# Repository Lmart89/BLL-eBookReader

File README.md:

# 📘 Bll Pilot

**Bll Pilot** es un proyecto de hardware libre y software de código abierto cuyo propósito es crear un lector de eBooks bíblicos de bajo consumo, enfocado en la simplicidad, portabilidad y larga duración de batería, diseñado especialmente para funcionar en zonas de baja conectividad o para uso personal/devocional.

> ✝️ *“Bll” representa muchas cosas: por un lado, “Biblia de Lectura Libre”, como un enfoque hacia el acceso abierto a la Palabra. Pero también son las iniciales de tres personas que inspiran profundamente este proyecto: Brillyd (esposa), Lemuel (hijo) y Luis (autor). "Pilot" señala que esta es la primera etapa o base para versiones futuras.*

---

## 🚀 Estado del proyecto

✨ **Actualización clave:** Al adoptar el módulo Core 3506B, el proyecto gana notables ventajas:

- 🧠 Procesador Quad-Core para mejor rendimiento multitarea
- 🎨 GPU integrada que mejora la fluidez gráfica incluso en pantallas E-Ink
- 🚀 Duplicación de RAM: de 256MB (anteriormente) a 512MB DDR3L
- 🔌 Mayor cantidad de pines IO (120), facilitando expansión sin conflictos

Estas mejoras colocan al *Bll Pilot* en una posición robusta para futuras funcionalidades sin sacrificar simplicidad ni eficiencia.

🔧 En desarrollo activo – Actualmente se encuentra en fase de diseño de hardware y primeros prototipos físicos.

La primera versión se centrará en:
- Lectura offline de textos bíblicos
- Bajo consumo y pantalla de tinta electrónica
- Interfaz minimalista para navegación fluida

---

## 🔩 Características técnicas

### 🧠 Módulo principal

- **Módulo base:** `Luckfox Core 3506B`
- **Chip:** Rockchip RK3506B
- **Procesador:** 3× Cortex-A7 + 1× Cortex-M0
- **RAM:** 512 MB DDR3L externa
- **Almacenamiento:** eMMC 8 GB por defecto
- **Almacenamiento soportado:** SPI Flash / eMMC / SDMMC
- **RM_IO:** 32 pines Rockchip Matrix IO
- **GPU:** Aceleración 2D/3D integrada
- **Conectividad:** USB host, soporte para Wi-Fi vía dongle USB (o versión Lyra W con Wi-Fi onboard)
- **Dimensiones:** 32 mm × 32 mm
- **Conectores:** 120 pines tipo *stamp hole*

### 🖥️ Pantalla
- Tipo: Pantalla E-Ink ED060XD4 (6 pulgadas, reciclada de Kindle)
- Interfaz: SPI
- Controlador: Requiere PMIC externo (como TPS65185)

### 🔌 Conectividad
- Táctil capacitivo (opcional, vía I2C)
- MicroSD (opcional)
- USB tipo C para carga y datos

### 🔋 Energía
- Batería de polímero de litio (con circuito de protección y carga)
- Circuito de bajo consumo en standby

---

## 📱 Software

El sistema estará basado en:
- 🐧 **Linux embebido** con Buildroot
- 🧱 Interfaz ligera (basada en LVGL o framebuffer directo)
- 📖 Motor de renderizado de textos optimizado para pantallas E-Ink
- 🕮 Indexación de la Biblia en diferentes versiones
- ⛺ Posibilidad de agregar documentos EPUB, TXT o formatos ligeros

---

## 🔓 Licencia

### 🔧 Hardware
Este proyecto está licenciado bajo la **CERN Open Hardware License v2 – Strongly Reciprocal (CERN OHL v2-S)**.

> Esto significa que cualquier derivado del hardware deberá mantenerse igualmente abierto y compartido con la comunidad.

### 💾 Software
El software se publica bajo la **GNU General Public License v3.0 (GPLv3)**.

> Esta licencia protege las libertades de uso, estudio, modificación y distribución del código, asegurando que permanezca siempre libre para todos los usuarios.

---

## 🧭 Visión futura

**Bll Pilot** nace como una plataforma que va más allá de ser un lector de eBooks:

- 📖 Herramienta de estudio bíblico portátil
- ⛺ Recurso para comunidades en zonas rurales o de difícil acceso
- 🛠️ Plataforma educativa para makers que deseen aprender sobre hardware embebido
- 📚 Dispositivo de lectura privada o devocional

Más adelante podrían desarrollarse versiones ampliadas, con audio, conectividad Wi-Fi permanente, y sincronización de notas o planes de lectura.

---

## 🙏 Créditos y agradecimientos

Proyecto impulsado por Luis E. Martínez S., con pasión por la electrónica, la Biblia, y el aprendizaje autodidacta.

Inspirado en la necesidad de crear herramientas útiles, abiertas y accesibles para todos.

> *Soli Deo Gloria.*

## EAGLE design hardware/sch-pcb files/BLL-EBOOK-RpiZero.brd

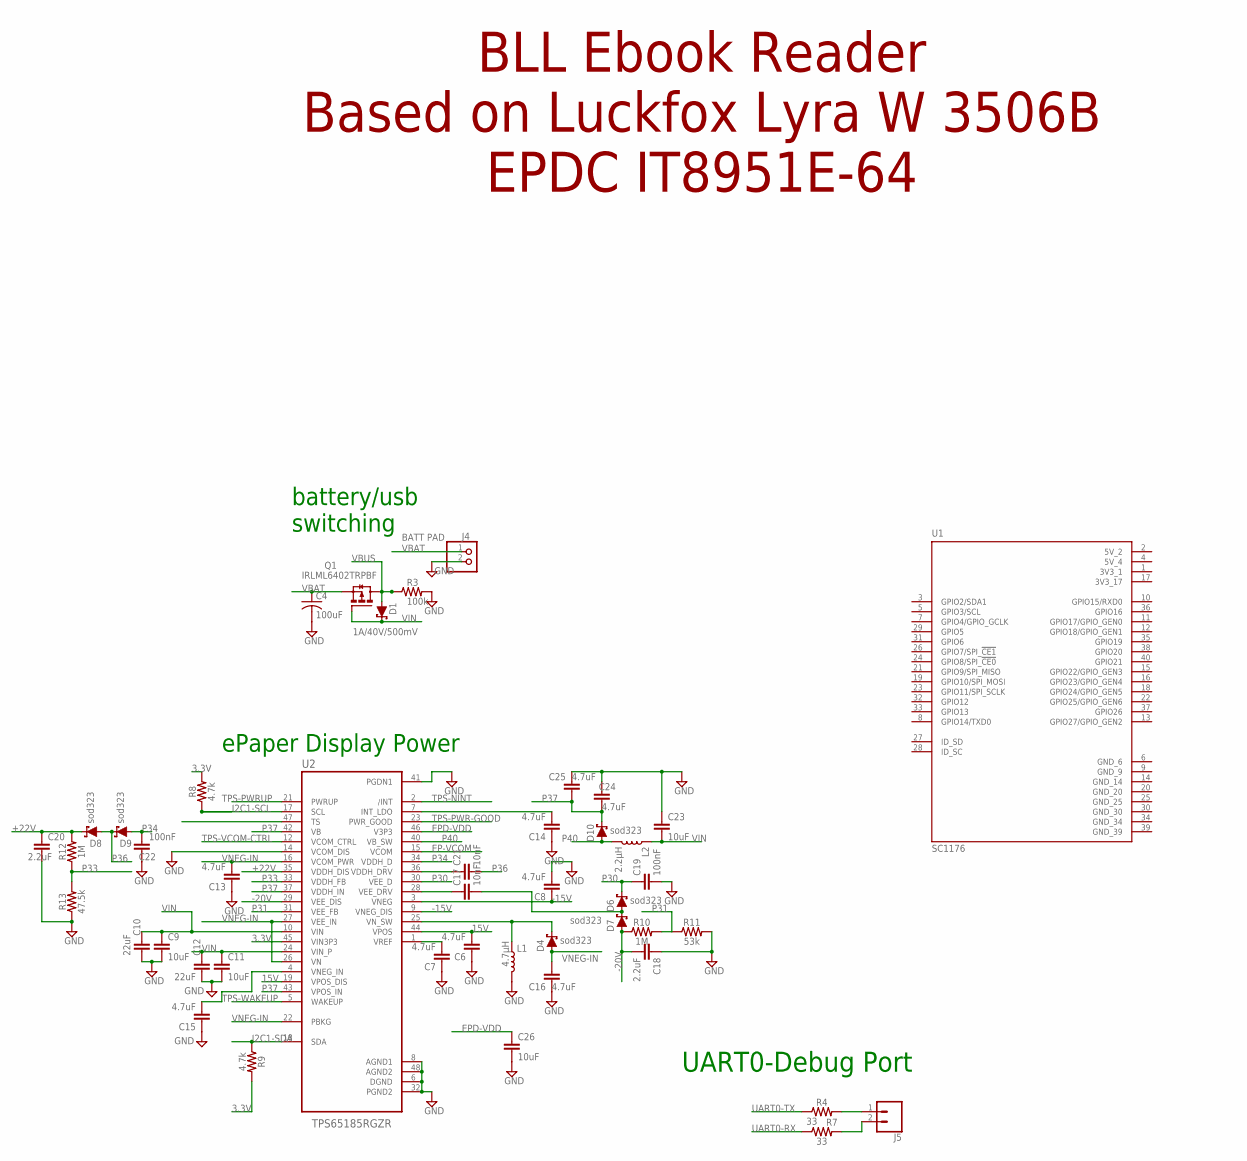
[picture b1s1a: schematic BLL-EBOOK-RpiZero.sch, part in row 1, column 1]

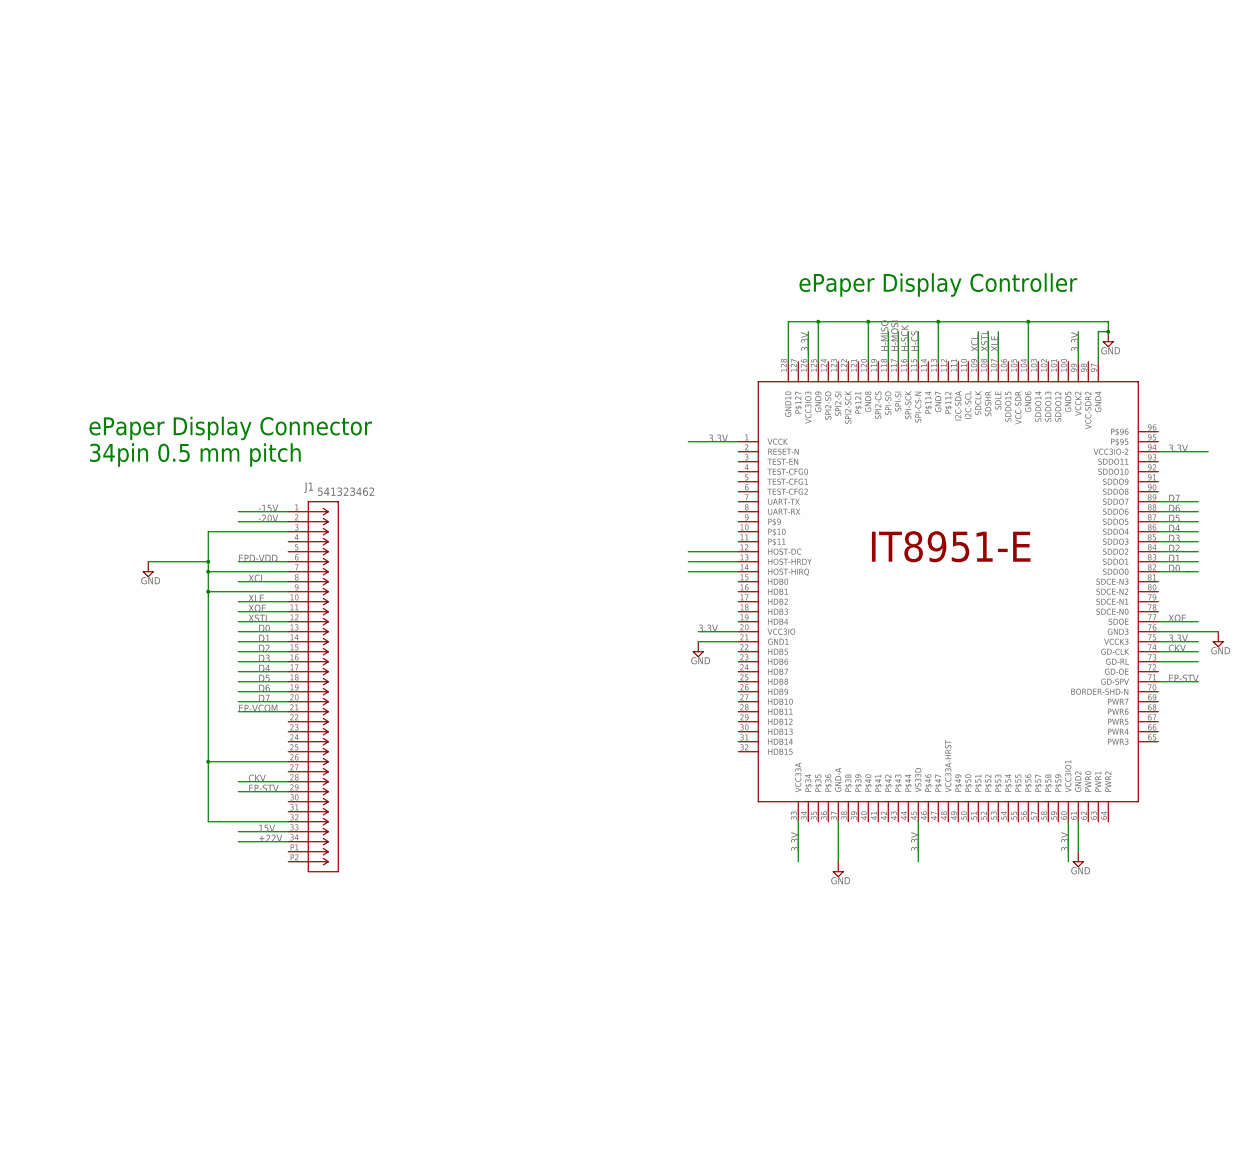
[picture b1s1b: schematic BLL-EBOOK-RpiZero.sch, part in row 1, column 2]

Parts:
C4: 100uF; C0603
C6, C7, C8, C13, C14, C15, C16, C24, C25: 4.7uF; 0603
C9, C11, C23, C26: 10uF; 0805
C10, C12: 22uF; 0805
C17, C21: 10nF; 0603
C18, C20: 2.2uF; 1206
C19, C22: 100nF; 0603
D1: 1A/40V/500mV; SMA-DIODE
D4, D6, D7, D8, D9, D10: sod323; SOD-323
J1: 541323462; CON_541323462_MOL
J4: BATT PAD; 1X02/90
J5: CONN_02LOCK; 1X02_LOCK
L1: 4.7μH; 1008(2520)
L2: 2.2μH; 0806
Q1: IRLML6402TRPBF; SOT23
R3: 100k; R0603
R4, R7: 33; 0603
R8, R9: 4.7k; 0603
R10, R12: 1M; 0603
R11: 53k; 0805
R13: 47.5k; 0805
U1: SC1176; MODULE_SC1176
U2: TPS65185RGZR; QFN50P700X700X100-49N
U$1: IT8951; LQFP128_STM

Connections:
3.3V: R8.2, R9.2, U2.45 (VIN3P3), U$1.1 (VCCK), U$1.20 (VCC3IO), U$1.33 (VCC33A), U$1.45 (VS33D), U$1.60 (VCC3IO1), U$1.75 (VCCK3), U$1.94 (VCC3IO-2), U$1.99 (VCCK2), U$1.126 (VCC3IO3)
3V3_1: U1.1 (3V3_1)
3V3_17: U1.17 (3V3_17)
5V_2: U1.2 (5V_2)
5V_4: U1.4 (5V_4)
15V: C6.2, J1.33, U2.19 (VPOS_DIS), U2.44 (VPOS)
+22V: C20.1, D8.C, J1.34, R12.2, U2.35 (VDDH_DIS)
-15V: C8.1, J1.1, U2.3 (VNEG), U2.9 (VNEG_DIS)
-20V: C18.2, D7.A, J1.2, R10.1, U2.29 (VEE_DIS)
CKV: J1.28, U$1.74 (GD-CLK)
D0: J1.13, U$1.82 (SDDO0)
D1: J1.14, U$1.83 (SDDO1)
D2: J1.15, U$1.84 (SDDO2)
D3: J1.16, U$1.85 (SDDO3)
D4: J1.17, U$1.86 (SDDO4)
D5: J1.18, U$1.87 (SDDO5)
D6: J1.19, U$1.88 (SDDO6)
D7: J1.20, U$1.89 (SDDO7)
EP-STV: J1.29, U$1.71 (GD-SPV)
EP-VCOM: J1.21, U2.15 (VCOM)
EPD-VDD: C26.1, J1.6, U2.46 (V3P3)
GND: C4.2, C6.1, C7.1, C8.2, C9.2, C10.2, C11.2, C12.2, C13.1, C14.1, C15.1, C16.1, C18.1, C19.2, C20.2, C22.1, C23.1, C24.2, C25.2, C26.2, J1.3, J1.7, J1.9, J1.26, J1.32, J4.2, L1.2, R3.2, R11.2, R13.1, U2.6 (DGND), U2.8 (AGND1), U2.14 (VCOM_DIS), U2.32 (PGND2), U2.41 (PGDN1), U2.48 (AGND2), U$1.21 (GND1), U$1.37 (GND-A), U$1.61 (GND2), U$1.76 (GND3), U$1.97 (GND4), U$1.104 (GND6), U$1.113 (GND7), U$1.120 (GND8), U$1.125 (GND9), U$1.128 (GND10)
GND_6: U1.6 (GND_6)
GND_9: U1.9 (GND_9)
GND_14: U1.14 (GND_14)
GND_20: U1.20 (GND_20)
GND_25: U1.25 (GND_25)
GND_30: U1.30 (GND_30)
GND_34: U1.34 (GND_34)
GND_39: U1.39 (GND_39)
H-CS: U$1.115 (SPI-CS-N)
H-MISO: U$1.118 (SPI-SO)
H-MOSI: U$1.117 (SPI-SI)
H-SCK: U$1.116 (SPI-SCK)
I2C1-SCL: R8.1, U2.17 (SCL)
I2C1-SDA: R9.1, U2.18 (SDA)
unnamed: J5.1, R4.2
unnamed: J5.2, R7.2
unnamed: C7.2, U2.1 (VREF)
unnamed: C15.2, U2.4 (VNEG_IN)
unnamed: C14.2, U2.7 (INT_LDO)
unnamed: D4.C, L1.1, U2.25 (VN_SW)
unnamed: C17.1, U2.28 (VEE_DRV)
unnamed: C17.2, D6.A, D7.C
unnamed: C21.1, U2.36 (VDDH_DRV)
P30: C19.1, D6.C, U2.30 (VEE_D)
P31: R10.2, R11.1, U2.31 (VEE_FB)
P33: R12.1, R13.2, U2.33 (VDDH_FB)
P34: C22.2, D9.A, U2.34 (VDDH_D)
P36: C21.2, D8.A, D9.C
P37: C24.1, C25.1, D10.C, U2.37 (VDDH_IN), U2.42 (VB), U2.43 (VPOS_IN)
P40: D10.A, L2.2, U2.40 (VB_SW)
TPS-NINT: U2.2 (/INT)
TPS-PWR-GOOD: U2.23 (PWR_GOOD)
TPS-PWRUP: U2.21 (PWRUP)
TPS-VCOM-CTRL: U2.12 (VCOM_CTRL)
TPS-WAKEUP: U2.5 (WAKEUP)
UART0-RX: R7.1
UART0-TX: R4.1
VBAT: C4.1, J4.1, Q1.2 (S)
VBUS: D1.A, Q1.3 (D), R3.1
VIN: C9.1, C10.1, C11.1, C12.1, C23.2, D1.C, L2.1, Q1.1 (G), U2.10 (VIN), U2.24 (VIN_P)
VNEG-IN: C13.2, C16.2, D4.A, U2.16 (VCOM_PWR), U2.22 (PBKG), U2.26 (VN), U2.27 (VEE_IN)
XCL: J1.8, U$1.109 (SDCLK)
XLE: J1.10, U$1.107 (SDLE)
XOE: J1.11, U$1.77 (SDOE)
XSTL: J1.12, U$1.108 (SDSHR)

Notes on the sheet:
battery/usb switching
ePaper Display Power
ePaper Display Connector 34pin 0.5 mm pitch
BLL Ebook Reader Based on Luckfox Lyra W 3506B EPDC IT8951E-64
ePaper Display Controller
UART0-Debug Port

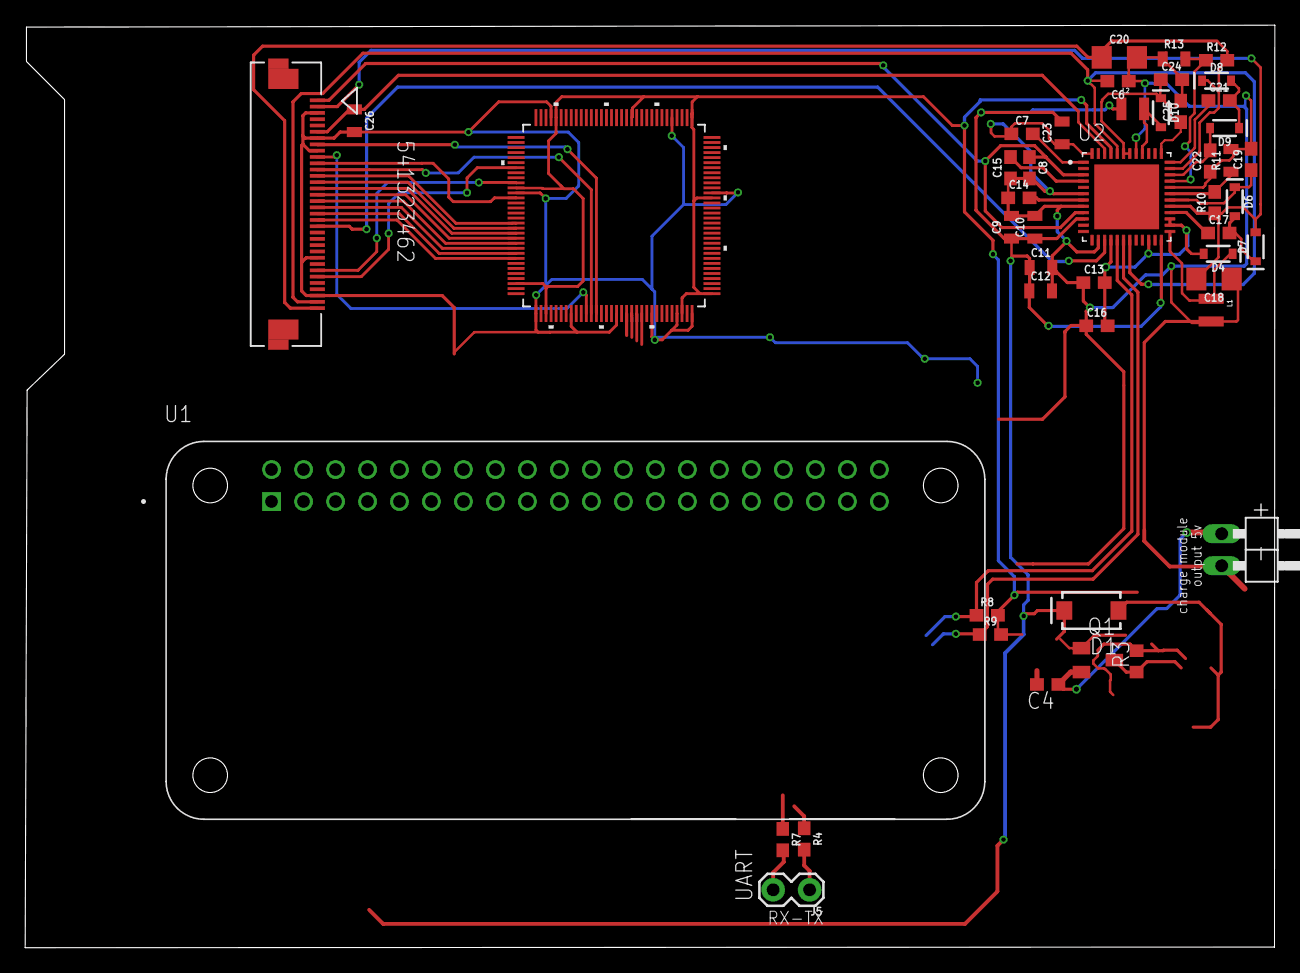
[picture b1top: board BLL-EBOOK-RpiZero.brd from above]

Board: 2 copper layers, 99.2 x 73.2 mm, 47 parts (0 on the bottom side), 44 nets.

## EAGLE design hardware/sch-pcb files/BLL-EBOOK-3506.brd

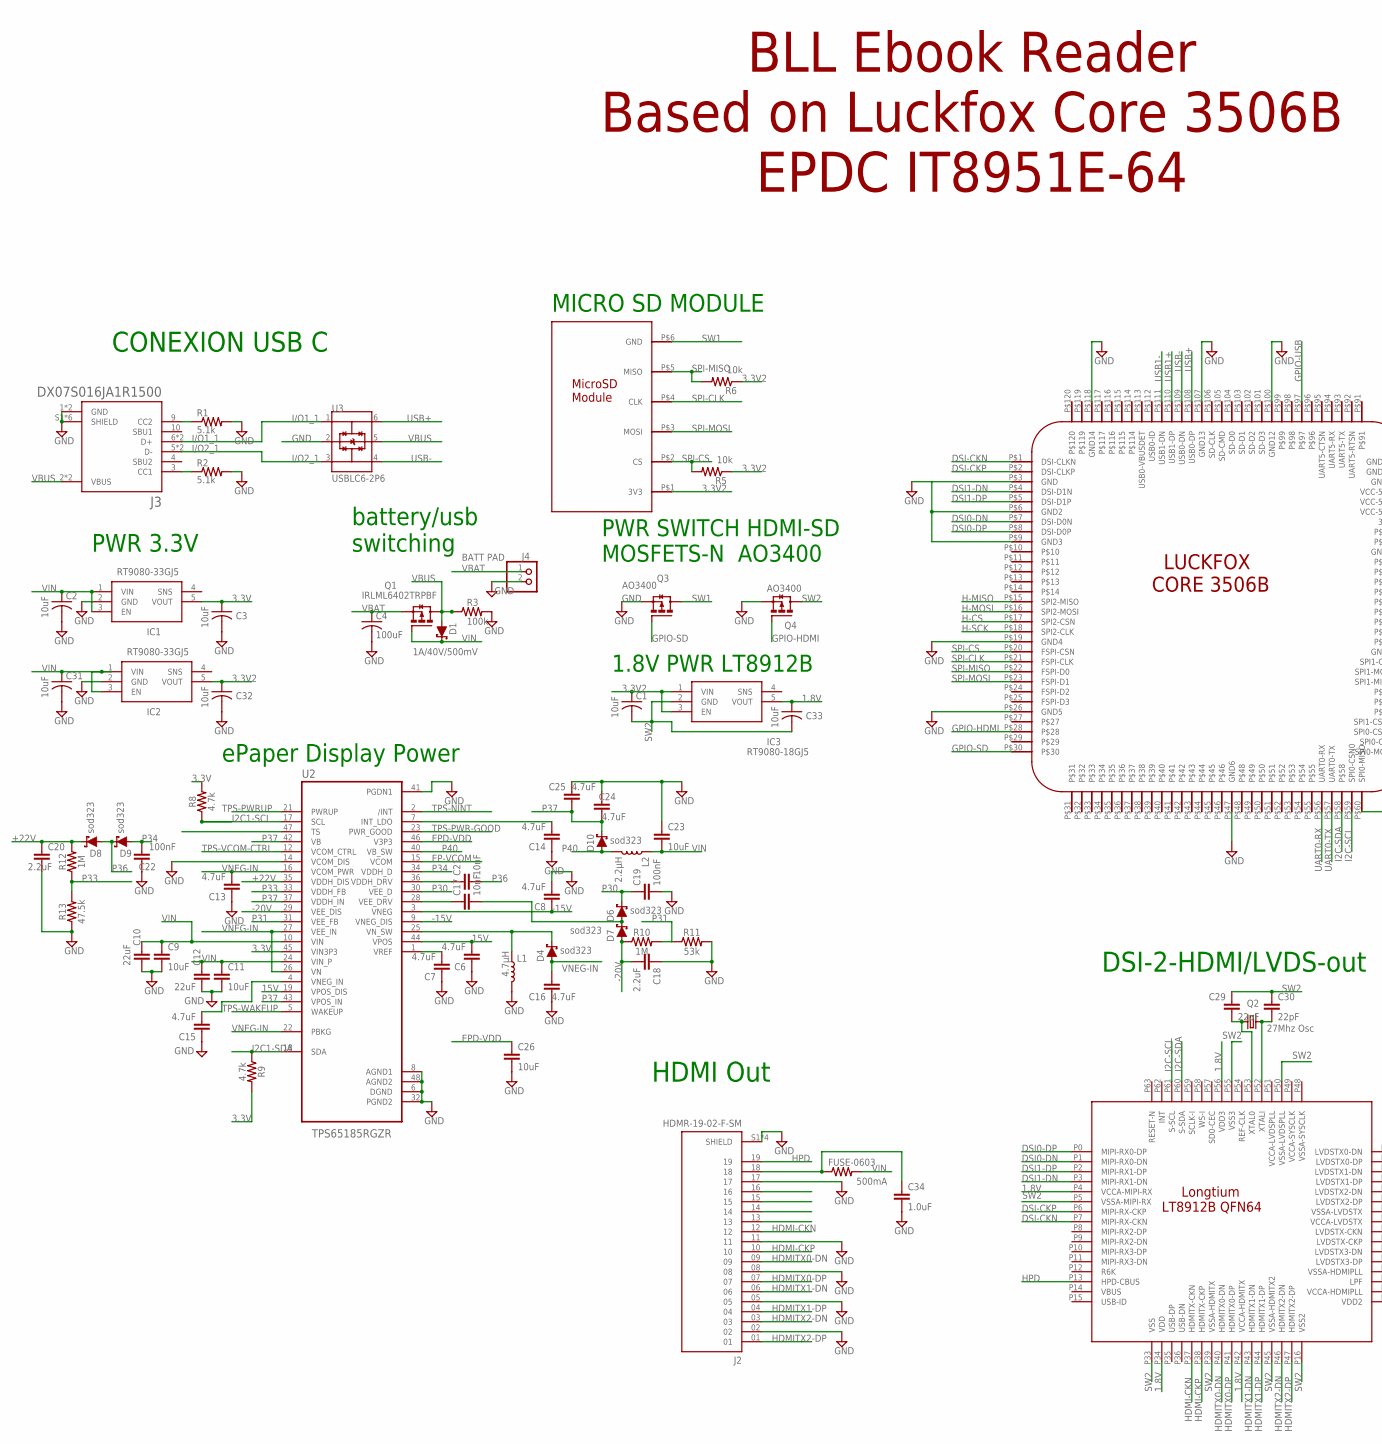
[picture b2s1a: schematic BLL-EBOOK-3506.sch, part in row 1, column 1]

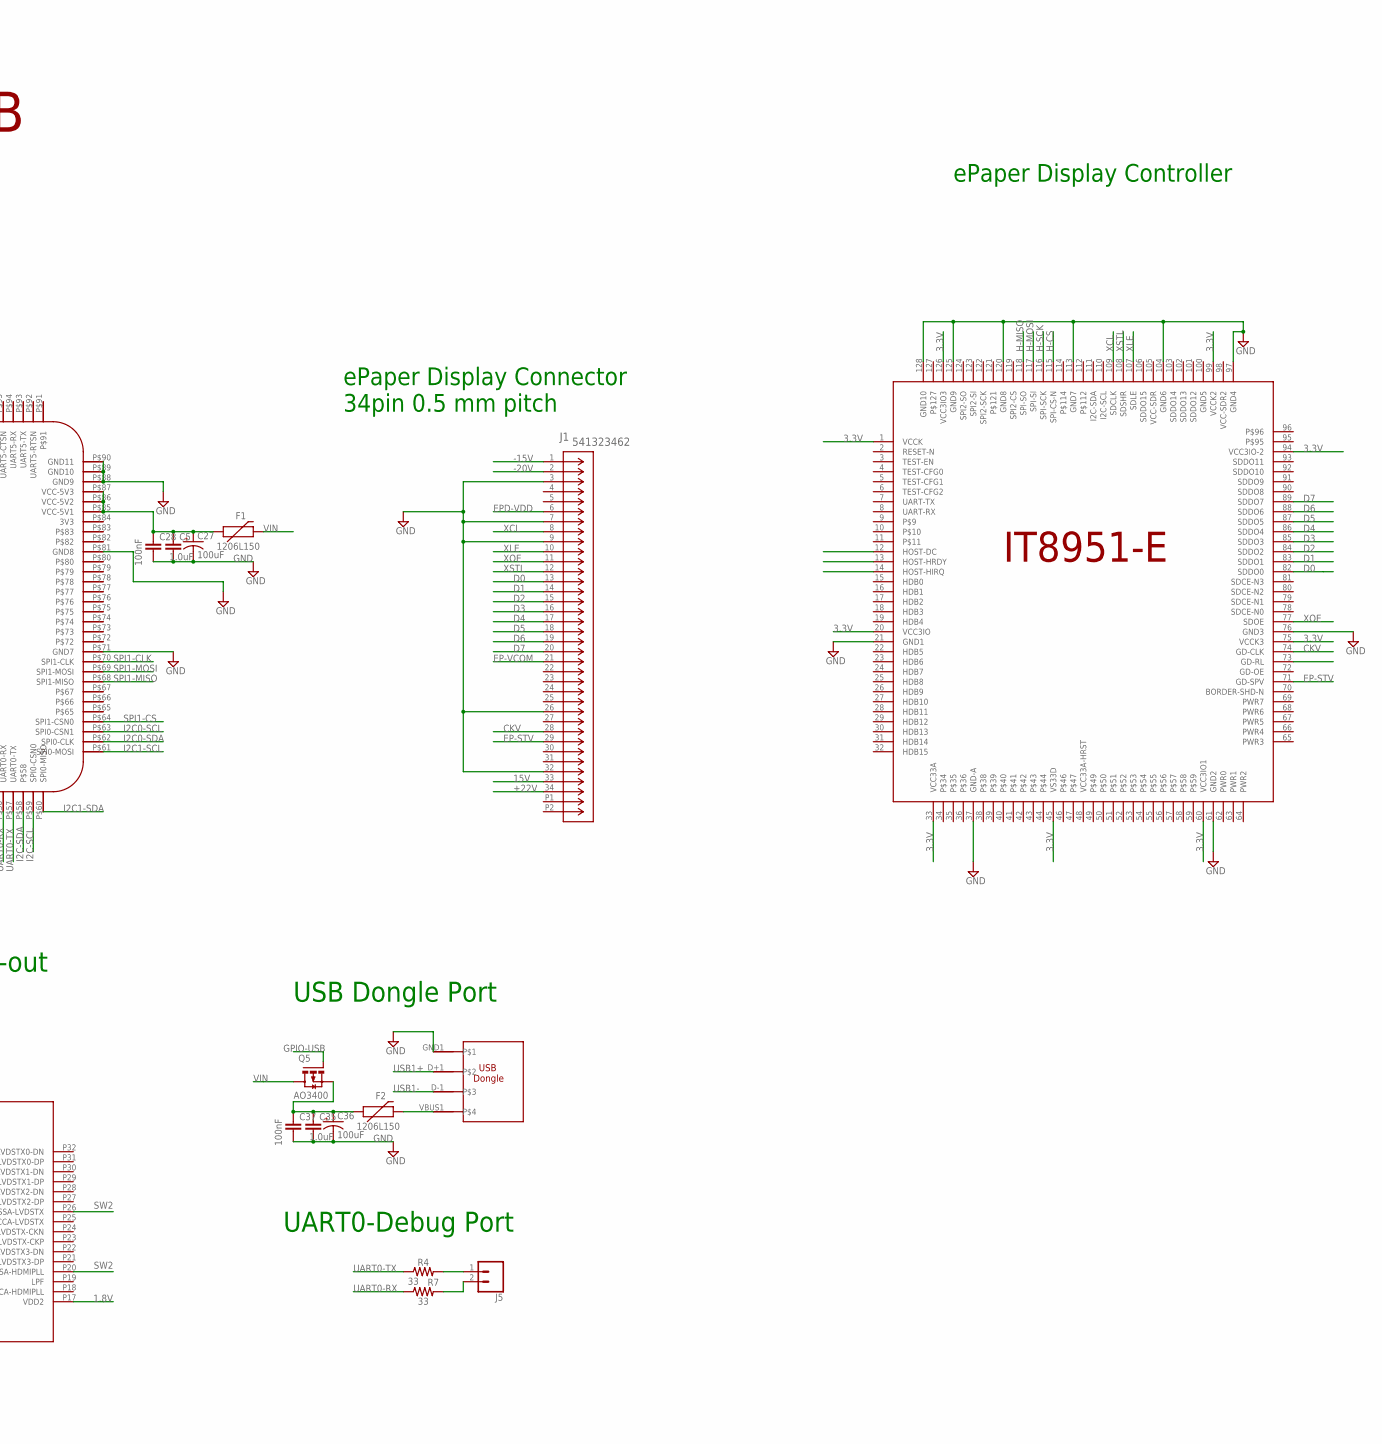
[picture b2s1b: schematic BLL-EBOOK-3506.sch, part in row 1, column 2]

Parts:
C1, C2, C3, C31, C32, C33: 10uF; C0603
C4: 100uF; C0603
C5, C34, C35: 1.0uF; 0603
C6, C7, C8, C13, C14, C15, C16, C24, C25: 4.7uF; 0603
C9, C11, C23, C26: 10uF; 0805
C10, C12: 22uF; 0805
C17, C21: 10nF; 0603
C18, C20: 2.2uF; 1206
C19, C22: 100nF; 0603
C27, C36: 100uF; EIA3528
C28, C37: 100nF; 0805
C29, C30: 22pF; 0603
D1: 1A/40V/500mV; SMA-DIODE
D4, D6, D7, D8, D9, D10: sod323; SOD-323
F1, F2: 1206L150; 1206
FUSE-0603: 500mA; 0603
IC1, IC2: RT9080-33GJ5; SOT94P280X100-5N
IC3: RT9080-18GJ5; SOT94P280X100-5N
J1: 541323462; CON_541323462_MOL
J2: HDMR-19-02-F-SM; SAMTEC_HDMR-19-02-F-SM
J3: DX07S016JA1R1500; JAE_DX07S016JA1R1500
J4: BATT PAD; 1X02/90
J5: CONN_02LOCK; 1X02_LOCK
L1: 4.7μH; 1008(2520)
L2: 2.2μH; 0806
LT8912: LT8912B
Q1: IRLML6402TRPBF; SOT23
Q2: 27Mhz Osc; 5.0X3.2_2
Q3, Q4, Q5: AO3400; SOT23
R1, R2: 5.1k; M0805
R3: 100k; R0603
R4, R7: 33; 0603
R5, R6: 10k; M0805
R8, R9: 4.7k; 0603
R10, R12: 1M; 0603
R11: 53k; 0805
R13: 47.5k; 0805
U2: TPS65185RGZR; QFN50P700X700X100-49N
U3: USBLC6-2P6; SOT50P160X60-6N
U$1: IT8951; LQFP128_STM
U$3: LUCKFOX_CORE3506; CORE3506
U$4: MICROSD-MODULE; MICROSD-MOD
U$5: USB-WIFI-DONGLE; USB-A-SMT-MALE

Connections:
1.8V: C33.1, IC3.5 (VOUT), LT8912.P4 (VCCA-MIPI-RX), LT8912.P17 (VDD2), LT8912.P34 (VDD), LT8912.P42 (VCCA-HDMITX), LT8912.P56 (VDD3)
3.3V: C3.1, IC1.5 (VOUT), R8.2, R9.2, U2.45 (VIN3P3), U$1.1 (VCCK), U$1.20 (VCC3IO), U$1.33 (VCC33A), U$1.45 (VS33D), U$1.60 (VCC3IO1), U$1.75 (VCCK3), U$1.94 (VCC3IO-2), U$1.99 (VCCK2), U$1.126 (VCC3IO3)
3.3V2: C1.1, C32.1, IC2.5 (VOUT), IC3.1 (VIN), IC3.3 (EN), R5.1, R6.1, U$4.P$1 (3V3)
15V: C6.2, J1.33, U2.19 (VPOS_DIS), U2.44 (VPOS)
+22V: C20.1, D8.C, J1.34, R12.2, U2.35 (VDDH_DIS)
-15V: C8.1, J1.1, U2.3 (VNEG), U2.9 (VNEG_DIS)
-20V: C18.2, D7.A, J1.2, R10.1, U2.29 (VEE_DIS)
CKV: J1.28, U$1.74 (GD-CLK)
D0: J1.13, U$1.82 (SDDO0)
D1: J1.14, U$1.83 (SDDO1)
D2: J1.15, U$1.84 (SDDO2)
D3: J1.16, U$1.85 (SDDO3)
D4: J1.17, U$1.86 (SDDO4)
D5: J1.18, U$1.87 (SDDO5)
D6: J1.19, U$1.88 (SDDO6)
D7: J1.20, U$1.89 (SDDO7)
DSI0-DN: LT8912.P1 (MIPI-RX0-DN), U$3.P$7 (DSI-D0N)
DSI0-DP: LT8912.P0 (MIPI-RX0-DP), U$3.P$8 (DSI-D0P)
DSI1-DN: LT8912.P3 (MIPI-RX1-DN), U$3.P$4 (DSI-D1N)
DSI1-DP: LT8912.P2 (MIPI-RX1-DP), U$3.P$5 (DSI-D1P)
DSI-CKN: LT8912.P7 (MIPI-RX-CKN), U$3.P$1 (DSI-CLKN)
DSI-CKP: LT8912.P6 (MIPI-RX-CKP), U$3.P$2 (DSI-CLKP)
EP-STV: J1.29, U$1.71 (GD-SPV)
EP-VCOM: J1.21, U2.15 (VCOM)
EPD-VDD: C26.1, J1.6, U2.46 (V3P3)
GND: C2.2, C3.2, C4.2, C5.2, C6.1, C7.1, C8.2, C9.2, C10.2, C11.2, C12.2, C13.1, C14.1, C15.1, C16.1, C18.1, C19.2, C20.2, C22.1, C23.1, C24.2, C25.2, C26.2, C27.C (-), C28.2, C31.2, C32.2, C34.2, C35.2, C36.C (-), C37.2, IC1.2 (GND), IC2.2 (GND), J1.3, J1.7, J1.9, J1.26, J1.32, J2.02, J2.05, J2.08, J2.11, J2.17, J2.S1 (SHIELD), J2.S2 (SHIELD), J2.S3 (SHIELD), J2.S4 (SHIELD), J3.1 (GND), J3.12 (GND), J3.S1 (SHIELD), J3.S2 (SHIELD), J3.S3 (SHIELD), J3.S4 (SHIELD), J3.S5 (SHIELD), J3.S6 (SHIELD), J4.2, L1.2, Q3.2 (S), Q4.2 (S), R1.2, R2.2, R3.2, R11.2, R13.1, U2.6 (DGND), U2.8 (AGND1), U2.14 (VCOM_DIS), U2.32 (PGND2), U2.41 (PGDN1), U2.48 (AGND2), U3.2 (GND), U$1.21 (GND1), U$1.37 (GND-A), U$1.61 (GND2), U$1.76 (GND3), U$1.97 (GND4), U$1.104 (GND6), U$1.113 (GND7), U$1.120 (GND8), U$1.125 (GND9), U$1.128 (GND10), U$3.P$3 (GND), U$3.P$6 (GND2), U$3.P$9 (GND3), U$3.P$19 (GND4), U$3.P$26 (GND5), U$3.P$47 (GND6), U$3.P$71 (GND7), U$3.P$81 (GND8), U$3.P$88 (GND9), U$3.P$89 (GND10), U$3.P$90 (GND11), U$3.P$100 (GND12), U$3.P$107 (GND13), U$3.P$118 (GND14), U$5.GND1
GPIO-HDMI: Q4.1 (G), U$3.P$28
GPIO-SD: Q3.1 (G), U$3.P$30
GPIO-USB: Q5.1 (G), U$3.P$97
H-CS: U$1.115 (SPI-CS-N), U$3.P$17 (SPI2-CSN)
H-MISO: U$1.118 (SPI-SO), U$3.P$15 (SPI2-MISO)
H-MOSI: U$1.117 (SPI-SI), U$3.P$16 (SPI2-MOSI)
H-SCK: U$1.116 (SPI-SCK), U$3.P$18 (SPI2-CLK)
HDMI-CKN: J2.12, LT8912.P37 (HDMITX-CKN)
HDMI-CKP: J2.10, LT8912.P38 (HDMITX-CKP)
HDMITX0-DN: J2.09, LT8912.P40 (HDMITX0-DN)
HDMITX0-DP: J2.07, LT8912.P41 (HDMITX0-DP)
HDMITX1-DN: J2.06, LT8912.P43 (HDMITX1-DN)
HDMITX1-DP: J2.04, LT8912.P44 (HDMITX1-DP)
HDMITX2-DN: J2.03, LT8912.P46 (HDMITX2-DN)
HDMITX2-DP: J2.01, LT8912.P47 (HDMITX2-DP)
HPD: J2.19, LT8912.P13 (HPD-CBUS)
I2C0-SCL: U$3.P$63 (SPI0-CSN1)
I2C0-SDA: U$3.P$62 (SPI0-CLK)
I2C1-SCL: R8.1, U2.17 (SCL), U$3.P$61 (SPI0-MOSI)
I2C1-SDA: R9.1, U2.18 (SDA), U$3.P$60 (SPI0-MISO)
I2C-SCL: LT8912.P61 (S-SCL), U$3.P$59 (SPI0-CSN0)
I2C-SDA: LT8912.P60 (S-SDA), U$3.P$58
I/O1_1: J3.6 (D+), J3.7 (D+), U3.1 (I/O1_1)
I/O2_1: J3.5 (D-), J3.8 (D-), U3.3 (I/O2_1)
unnamed: C29.2, LT8912.P53 (XTAL0), Q2.1
unnamed: C30.2, LT8912.P52 (XTALI), Q2.2
unnamed: J3.3 (CC1), R2.1
unnamed: J3.9 (CC2), R1.1
unnamed: F2.2, U$5.VBUS1
unnamed: J5.1, R4.2
unnamed: J5.2, R7.2
unnamed: C7.2, U2.1 (VREF)
unnamed: C15.2, U2.4 (VNEG_IN)
unnamed: C14.2, U2.7 (INT_LDO)
unnamed: D4.C, L1.1, U2.25 (VN_SW)
unnamed: C17.1, U2.28 (VEE_DRV)
unnamed: C17.2, D6.A, D7.C
unnamed: C21.1, U2.36 (VDDH_DRV)
unnamed: C34.1, FUSE-0603.1, J2.18
P: C5.1, C27.A (+), C28.1, F1.1, U$3.P$85 (VCC-5V1), U$3.P$86 (VCC-5V2), U$3.P$87 (VCC-5V3)
P1: C35.1, C36.A (+), C37.1, F2.1, Q5.2 (S)
P30: C19.1, D6.C, U2.30 (VEE_D)
P31: R10.2, R11.1, U2.31 (VEE_FB)
P33: R12.1, R13.2, U2.33 (VDDH_FB)
P34: C22.2, D9.A, U2.34 (VDDH_D)
P36: C21.2, D8.A, D9.C
P37: C24.1, C25.1, D10.C, U2.37 (VDDH_IN), U2.42 (VB), U2.43 (VPOS_IN)
P40: D10.A, L2.2, U2.40 (VB_SW)
SPI1-CLK: U$3.P$70 (SPI1-CLK)
SPI1-CS: U$3.P$64 (SPI1-CSN0)
SPI1-MISO: U$3.P$68 (SPI1-MISO)
SPI1-MOSI: U$3.P$69 (SPI1-MOSI)
SPI-CLK: U$3.P$21 (FSPI-CLK), U$4.P$4 (CLK)
SPI-CS: R5.2, U$3.P$20 (FSPI-CSN), U$4.P$2 (CS)
SPI-MISO: R6.2, U$3.P$22 (FSPI-D0), U$4.P$5 (MISO)
SPI-MOSI: U$3.P$23 (FSPI-D1), U$4.P$3 (MOSI)
SW1: Q3.3 (D), U$4.P$6 (GND)
SW2: C1.2, C29.1, C30.1, C33.2, IC3.2 (GND), LT8912.P5 (VSSA-MIPI-RX), LT8912.P16 (VSS2), LT8912.P20 (VSSA-HDMIPLL), LT8912.P26 (VSSA-LVDSTX), LT8912.P33 (VSS), LT8912.P39 (VSSA-HDMITX), LT8912.P45 (VSSA-HDMITX2), LT8912.P50 (VSSA-LVDSPLL), LT8912.P55 (VSS3), Q4.3 (D)
TPS-NINT: U2.2 (/INT)
TPS-PWR-GOOD: U2.23 (PWR_GOOD)
TPS-PWRUP: U2.21 (PWRUP)
TPS-VCOM-CTRL: U2.12 (VCOM_CTRL)
TPS-WAKEUP: U2.5 (WAKEUP)
UART0-RX: R7.1, U$3.P$56 (UART0-RX)
UART0-TX: R4.1, U$3.P$57 (UART0-TX)
USB1+: U$3.P$110 (USB1-DP), U$5.D+1
USB1-: U$3.P$111 (USB1-DN), U$5.D-1
USB+: U3.6 (I/O1_2), U$3.P$108 (USB0-DP)
USB-: U3.4 (I/O2_2), U$3.P$109 (USB0-DN)
VBAT: C4.1, J4.1, Q1.2 (S)
VBUS: D1.A, J3.2 (VBUS), J3.11 (VBUS), Q1.3 (D), R3.1, U3.5 (VBUS)
VIN: C2.1, C9.1, C10.1, C11.1, C12.1, C23.2, C31.1, D1.C, F1.2, FUSE-0603.2, IC1.1 (VIN), IC1.3 (EN), IC2.1 (VIN), IC2.3 (EN), L2.1, Q1.1 (G), Q5.3 (D), U2.10 (VIN), U2.24 (VIN_P)
VNEG-IN: C13.2, C16.2, D4.A, U2.16 (VCOM_PWR), U2.22 (PBKG), U2.26 (VN), U2.27 (VEE_IN)
XCL: J1.8, U$1.109 (SDCLK)
XLE: J1.10, U$1.107 (SDLE)
XOE: J1.11, U$1.77 (SDOE)
XSTL: J1.12, U$1.108 (SDSHR)

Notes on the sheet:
CONEXION USB C
MICRO SD MODULE
PWR 3.3V
battery/usb switching
ePaper Display Power
ePaper Display Connector 34pin 0.5 mm pitch
BLL Ebook Reader Based on Luckfox Core 3506B EPDC IT8951E-64
ePaper Display Controller
DSI-2-HDMI/LVDS-out
PWR SWITCH HDMI-SD MOSFETS-N AO3400
1.8V PWR LT8912B
HDMI Out
USB Dongle Port
UART0-Debug Port

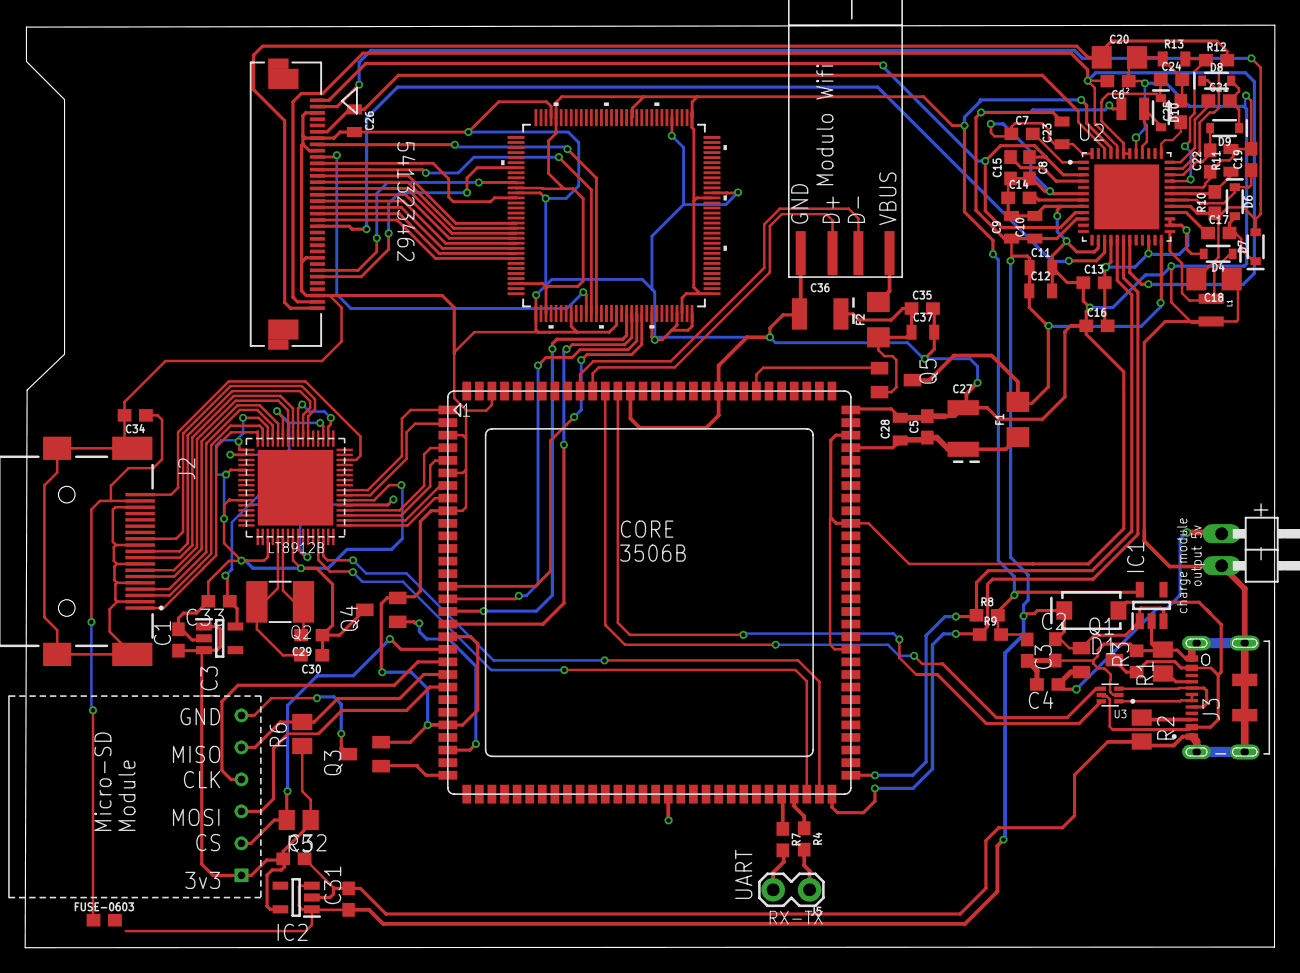
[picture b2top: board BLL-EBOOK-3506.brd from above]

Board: 2 copper layers, 99.2 x 73.2 mm, 82 parts (0 on the bottom side), 92 nets.

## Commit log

2025-06-03 Update LICENSE
2025-06-22 Update README.md
    added readme info and a development roadmap.
2025-06-28 UPDATE FILES
    ADD PCB FILES AND EAGLE CUSTOM LIBS
2025-06-28 resource docs added
2025-06-28 new pcb and sch files
2025-06-30 reorganized of repository structure
2025-07-04 new bible module
2025-07-05 update rv60 bible text
2025-07-06 Bibletool updated readme and bible modules
2025-07-06 Update apps readme.md
    extended readme version with instructions on how to develope, configure, compile and install or modify apps for the Bll eBook Reader
2025-07-06 Rename BibleTool.md to Readme.md
2025-07-06 instructions for developing and compiling apps
2025-07-08 complete version of RV60 Bible and tools for validation of files
2025-07-09 Rename README.md to README-old.md
2025-07-13 Update readme.md
    Bible de log for documentation
2025-07-13 last version of rv60.csv with new text corrections
    deleted duplicated verses, and fixed some verses leng untill Exodus book.
    still need some fixes that will be available as soon as possible.
    - added spanish rv1909 bible (rv09) as a trusted source for local comparison of verses and checking integrity of rv60 spanish bible. also available as a bible version.
2025-07-17 new platform build
2025-07-27 added epdc it8951e-64
2025-07-27 new core design for bll pilot
2025-08-04 new ic datasheets
2025-08-04 core 3506B pinout list
2025-08-04 RK3506B official Datasheet
2025-08-05 new schematic update
2025-08-05 lt8912b library added
2025-08-10 new sch and brd design update
2025-08-10 updated pcb top
2025-08-12 updated pcb and schematic design
2025-08-16 updated pcb and schematic files.
2025-09-16 new eagle library added for rpi zero like boards
2025-09-17 new pcb design for new lyra w model

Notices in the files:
parts and their libraries:
SparkFun-DiscreteSemi: Licensing: Creative Commons ShareAlike 4.0 International - https://creativecommons.org/licenses/by-sa/4.0
crystal-geyer_V1_0: Copyright: Geyer-Electronic
